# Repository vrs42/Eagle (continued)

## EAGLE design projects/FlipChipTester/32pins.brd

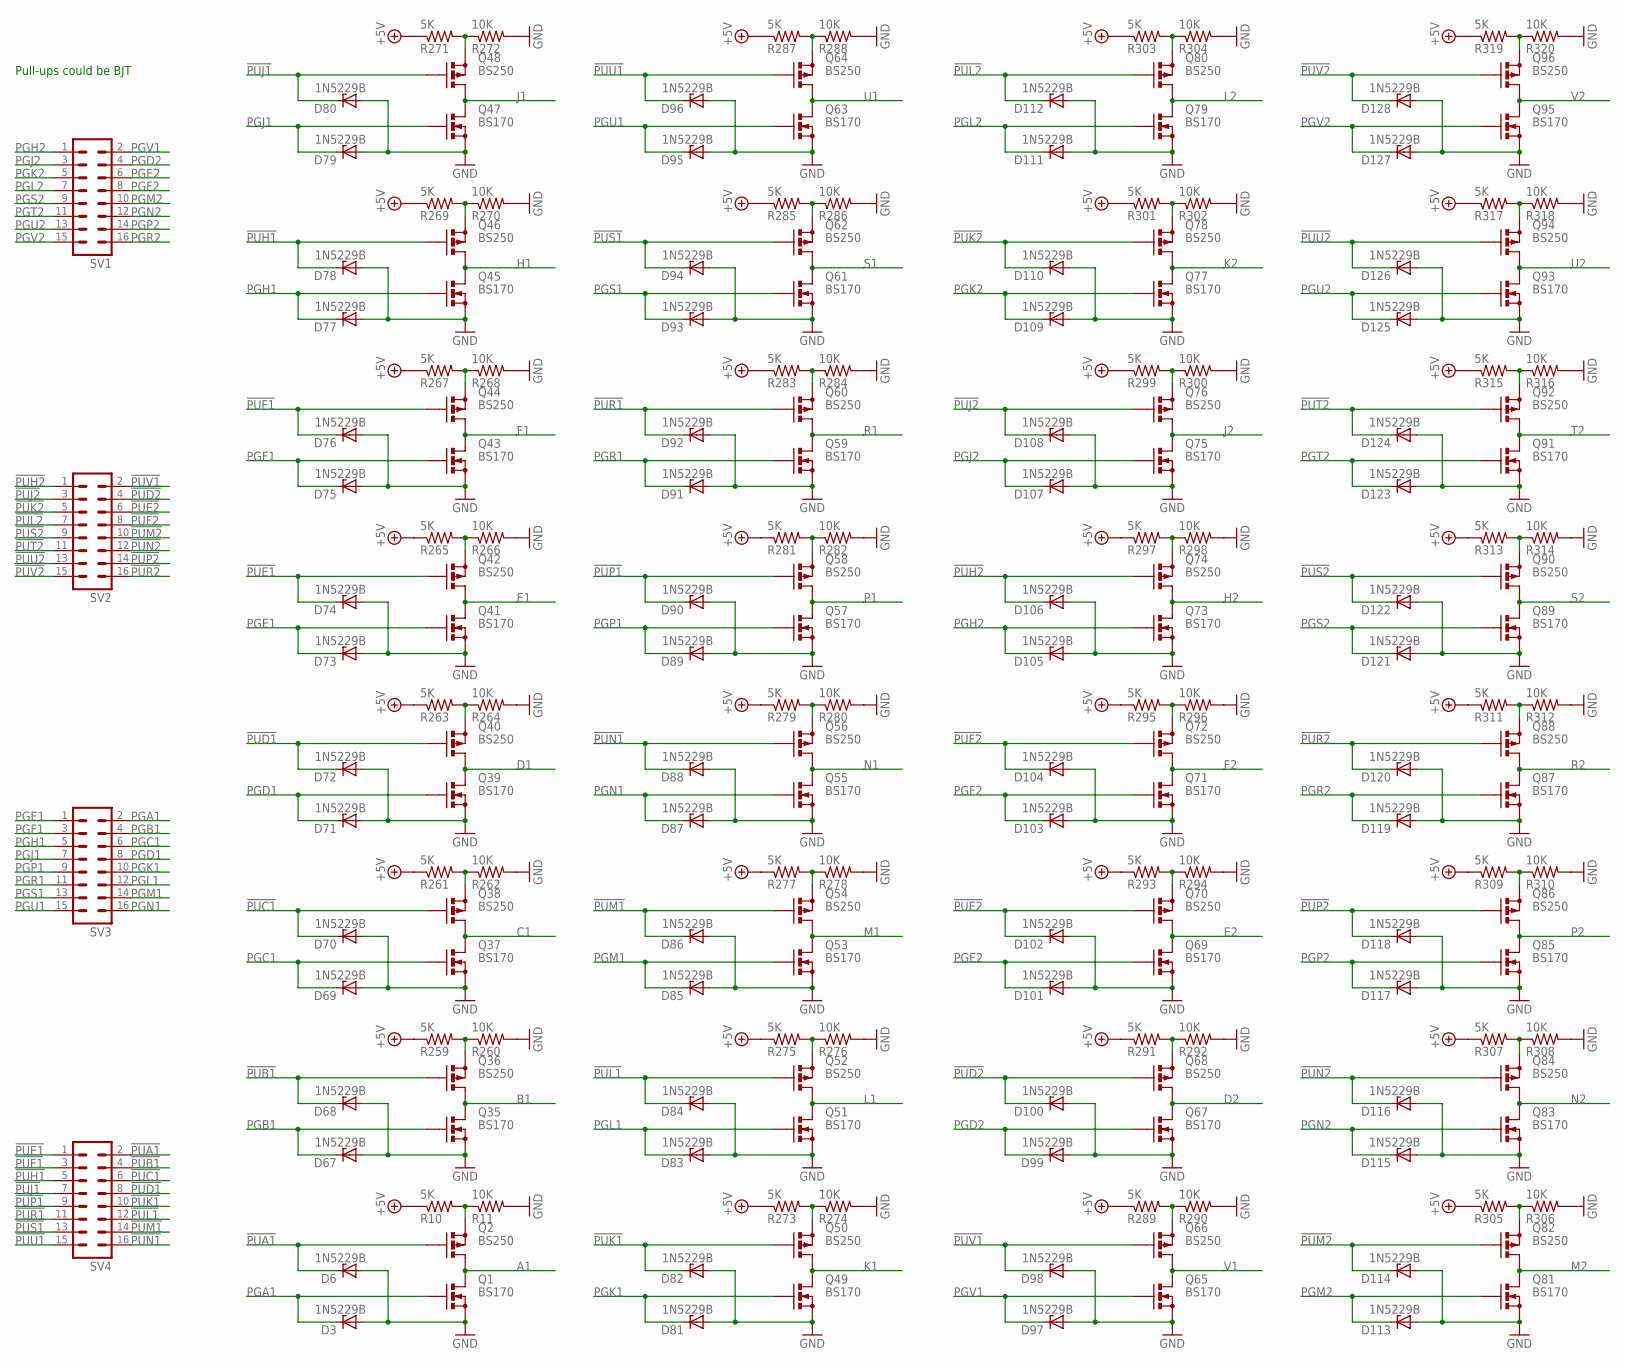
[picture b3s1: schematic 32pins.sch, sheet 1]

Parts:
D3, D6, D67, D68, D69, D70, D71, D72, D73, D74, D75, D76, D77, D78, D79, D80, D81, D82, D83, D84, D85, D86, D87, D88, D89, D90, D91, D92, D93, D94, D95, D96, D97, D98, D99, D100, D101, D102, D103, D104, D105, D106, D107, D108, D109, D110, D111, D112, D113, D114, D115, D116, D117, D118, D119, D120, D121, D122, D123, D124, D125, D126, D127, D128: 1N5229B; ZDIO-2.5
Q1, Q35, Q37, Q39, Q41, Q43, Q45, Q47, Q49, Q51, Q53, Q55, Q57, Q59, Q61, Q63, Q65, Q67, Q69, Q71, Q73, Q75, Q77, Q79, Q81, Q83, Q85, Q87, Q89, Q91, Q93, Q95: BS170; SOT54E
Q2, Q36, Q38, Q40, Q42, Q44, Q46, Q48, Q50, Q52, Q54, Q56, Q58, Q60, Q62, Q64, Q66, Q68, Q70, Q72, Q74, Q76, Q78, Q80, Q82, Q84, Q86, Q88, Q90, Q92, Q94, Q96: BS250; SOT54E
R10, R259, R261, R263, R265, R267, R269, R271, R273, R275, R277, R279, R281, R283, R285, R287, R289, R291, R293, R295, R297, R299, R301, R303, R305, R307, R309, R311, R313, R315, R317, R319: 5K; 0207/2V
R11, R260, R262, R264, R266, R268, R270, R272, R274, R276, R278, R280, R282, R284, R286, R288, R290, R292, R294, R296, R298, R300, R302, R304, R306, R308, R310, R312, R314, R316, R318, R320: 10K; 0207/2V
SV1, SV2, SV3, SV4: MA08-2

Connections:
!PUA1: D6.C, Q2.G, SV4.2
!PUB1: D68.C, Q36.G, SV4.4
!PUC1: D70.C, Q38.G, SV4.6
!PUD1: D72.C, Q40.G, SV4.8
!PUD2: D100.C, Q68.G, SV2.4
!PUE1: D74.C, Q42.G, SV4.1
!PUE2: D102.C, Q70.G, SV2.6
!PUF1: D76.C, Q44.G, SV4.3
!PUF2: D104.C, Q72.G, SV2.8
!PUH1: D78.C, Q46.G, SV4.5
!PUH2: D106.C, Q74.G, SV2.1
!PUJ1: D80.C, Q48.G, SV4.7
!PUJ2: D108.C, Q76.G, SV2.3
!PUK1: D82.C, Q50.G, SV4.10
!PUK2: D110.C, Q78.G, SV2.5
!PUL1: D84.C, Q52.G, SV4.12
!PUL2: D112.C, Q80.G, SV2.7
!PUM1: D86.C, Q54.G, SV4.14
!PUM2: D114.C, Q82.G, SV2.10
!PUN1: D88.C, Q56.G, SV4.16
!PUN2: D116.C, Q84.G, SV2.12
!PUP1: D90.C, Q58.G, SV4.9
!PUP2: D118.C, Q86.G, SV2.14
!PUR1: D92.C, Q60.G, SV4.11
!PUR2: D120.C, Q88.G, SV2.16
!PUS1: D94.C, Q62.G, SV4.13
!PUS2: D122.C, Q90.G, SV2.9
!PUT2: D124.C, Q92.G, SV2.11
!PUU1: D96.C, Q64.G, SV4.15
!PUU2: D126.C, Q94.G, SV2.13
!PUV1: D98.C, Q66.G, SV2.2
!PUV2: D128.C, Q96.G, SV2.15
+5V: R10.1, R259.1, R261.1, R263.1, R265.1, R267.1, R269.1, R271.1, R273.1, R275.1, R277.1, R279.1, R281.1, R283.1, R285.1, R287.1, R289.1, R291.1, R293.1, R295.1, R297.1, R299.1, R301.1, R303.1, R305.1, R307.1, R309.1, R311.1, R313.1, R315.1, R317.1, R319.1; also elsewhere on the board
A1: Q1.D, Q2.D; also elsewhere on the board
B1: Q35.D, Q36.D; also elsewhere on the board
C1: Q37.D, Q38.D; also elsewhere on the board
D1: Q39.D, Q40.D; also elsewhere on the board
D2: Q67.D, Q68.D; also elsewhere on the board
E1: Q41.D, Q42.D; also elsewhere on the board
E2: Q69.D, Q70.D; also elsewhere on the board
F1: Q43.D, Q44.D; also elsewhere on the board
F2: Q71.D, Q72.D; also elsewhere on the board
GND: D3.A, D6.A, D67.A, D68.A, D69.A, D70.A, D71.A, D72.A, D73.A, D74.A, D75.A, D76.A, D77.A, D78.A, D79.A, D80.A, D81.A, D82.A, D83.A, D84.A, D85.A, D86.A, D87.A, D88.A, D89.A, D90.A, D91.A, D92.A, D93.A, D94.A, D95.A, D96.A, D97.A, D98.A, D99.A, D100.A, D101.A, D102.A, D103.A, D104.A, D105.A, D106.A, D107.A, D108.A, D109.A, D110.A, D111.A, D112.A, D113.A, D114.A, D115.A, D116.A, D117.A, D118.A, D119.A, D120.A, D121.A, D122.A, D123.A, D124.A, D125.A, D126.A, D127.A, D128.A, Q1.S, Q35.S, Q37.S, Q39.S, Q41.S, Q43.S, Q45.S, Q47.S, Q49.S, Q51.S, Q53.S, Q55.S, Q57.S, Q59.S, Q61.S, Q63.S, Q65.S, Q67.S, Q69.S, Q71.S, Q73.S, Q75.S, Q77.S, Q79.S, Q81.S, Q83.S, Q85.S, Q87.S, Q89.S, Q91.S, Q93.S, Q95.S, R11.2, R260.2, R262.2, R264.2, R266.2, R268.2, R270.2, R272.2, R274.2, R276.2, R278.2, R280.2, R282.2, R284.2, R286.2, R288.2, R290.2, R292.2, R294.2, R296.2, R298.2, R300.2, R302.2, R304.2, R306.2, R308.2, R310.2, R312.2, R314.2, R316.2, R318.2, R320.2; also elsewhere on the board
H1: Q45.D, Q46.D; also elsewhere on the board
H2: Q73.D, Q74.D; also elsewhere on the board
J1: Q47.D, Q48.D; also elsewhere on the board
J2: Q75.D, Q76.D; also elsewhere on the board
K1: Q49.D, Q50.D; also elsewhere on the board
K2: Q77.D, Q78.D; also elsewhere on the board
L1: Q51.D, Q52.D; also elsewhere on the board
L2: Q79.D, Q80.D; also elsewhere on the board
M1: Q53.D, Q54.D; also elsewhere on the board
M2: Q81.D, Q82.D; also elsewhere on the board
N1: Q55.D, Q56.D; also elsewhere on the board
N2: Q83.D, Q84.D; also elsewhere on the board
unnamed: Q2.S, R10.2, R11.1
unnamed: Q36.S, R259.2, R260.1
unnamed: Q38.S, R261.2, R262.1
unnamed: Q40.S, R263.2, R264.1
unnamed: Q42.S, R265.2, R266.1
unnamed: Q44.S, R267.2, R268.1
unnamed: Q46.S, R269.2, R270.1
unnamed: Q48.S, R271.2, R272.1
unnamed: Q50.S, R273.2, R274.1
unnamed: Q52.S, R275.2, R276.1
unnamed: Q54.S, R277.2, R278.1
unnamed: Q56.S, R279.2, R280.1
unnamed: Q58.S, R281.2, R282.1
unnamed: Q60.S, R283.2, R284.1
unnamed: Q62.S, R285.2, R286.1
unnamed: Q64.S, R287.2, R288.1
unnamed: Q66.S, R289.2, R290.1
unnamed: Q68.S, R291.2, R292.1
unnamed: Q70.S, R293.2, R294.1
unnamed: Q72.S, R295.2, R296.1
unnamed: Q74.S, R297.2, R298.1
unnamed: Q76.S, R299.2, R300.1
unnamed: Q78.S, R301.2, R302.1
unnamed: Q80.S, R303.2, R304.1
unnamed: Q82.S, R305.2, R306.1
unnamed: Q84.S, R307.2, R308.1
unnamed: Q86.S, R309.2, R310.1
unnamed: Q88.S, R311.2, R312.1
unnamed: Q90.S, R313.2, R314.1
unnamed: Q92.S, R315.2, R316.1
unnamed: Q94.S, R317.2, R318.1
unnamed: Q96.S, R319.2, R320.1
P1: Q57.D, Q58.D; also elsewhere on the board
P2: Q85.D, Q86.D; also elsewhere on the board
PGA1: D3.C, Q1.G, SV3.2
PGB1: D67.C, Q35.G, SV3.4
PGC1: D69.C, Q37.G, SV3.6
PGD1: D71.C, Q39.G, SV3.8
PGD2: D99.C, Q67.G, SV1.4
PGE1: D73.C, Q41.G, SV3.1
PGE2: D101.C, Q69.G, SV1.6
PGF1: D75.C, Q43.G, SV3.3
PGF2: D103.C, Q71.G, SV1.8
PGH1: D77.C, Q45.G, SV3.5
PGH2: D105.C, Q73.G, SV1.1
PGJ1: D79.C, Q47.G, SV3.7
PGJ2: D107.C, Q75.G, SV1.3
PGK1: D81.C, Q49.G, SV3.10
PGK2: D109.C, Q77.G, SV1.5
PGL1: D83.C, Q51.G, SV3.12
PGL2: D111.C, Q79.G, SV1.7
PGM1: D85.C, Q53.G, SV3.14
PGM2: D113.C, Q81.G, SV1.10
PGN1: D87.C, Q55.G, SV3.16
PGN2: D115.C, Q83.G, SV1.12
PGP1: D89.C, Q57.G, SV3.9
PGP2: D117.C, Q85.G, SV1.14
PGR1: D91.C, Q59.G, SV3.11
PGR2: D119.C, Q87.G, SV1.16
PGS1: D93.C, Q61.G, SV3.13
PGS2: D121.C, Q89.G, SV1.9
PGT2: D123.C, Q91.G, SV1.11
PGU1: D95.C, Q63.G, SV3.15
PGU2: D125.C, Q93.G, SV1.13
PGV1: D97.C, Q65.G, SV1.2
PGV2: D127.C, Q95.G, SV1.15
R1: Q59.D, Q60.D; also elsewhere on the board
R2: Q87.D, Q88.D; also elsewhere on the board
S1: Q61.D, Q62.D; also elsewhere on the board
S2: Q89.D, Q90.D; also elsewhere on the board
T2: Q91.D, Q92.D; also elsewhere on the board
U1: Q63.D, Q64.D; also elsewhere on the board
U2: Q93.D, Q94.D; also elsewhere on the board
V1: Q65.D, Q66.D; also elsewhere on the board
V2: Q95.D, Q96.D; also elsewhere on the board

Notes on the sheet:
Pull-ups could be BJT

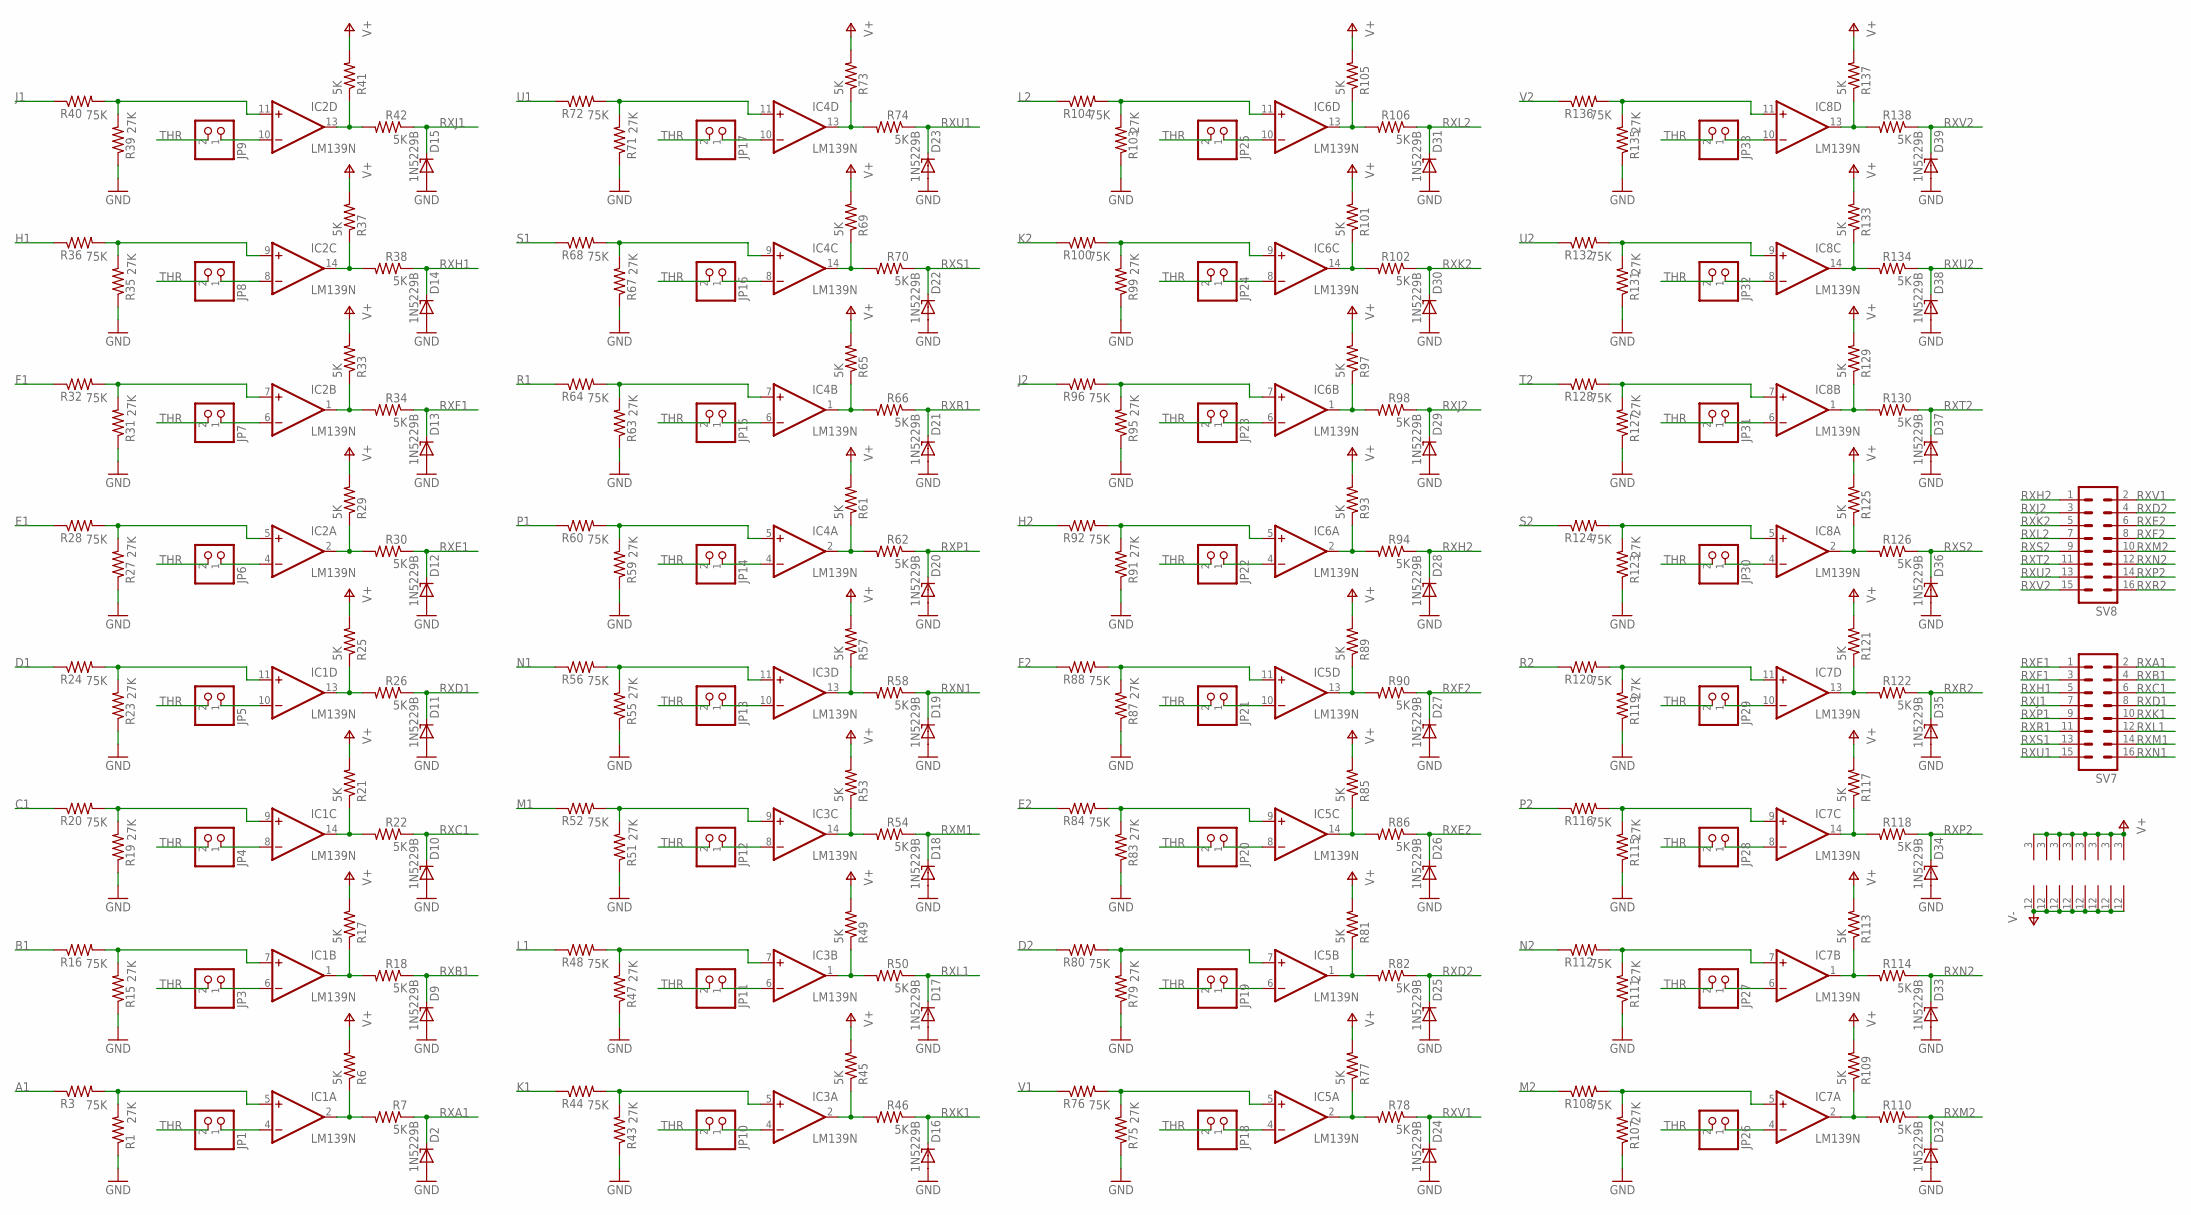
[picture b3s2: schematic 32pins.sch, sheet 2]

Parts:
D2, D9, D10, D11, D12, D13, D14, D15, D16, D17, D18, D19, D20, D21, D22, D23, D24, D25, D26, D27, D28, D29, D30, D31, D32, D33, D34, D35, D36, D37, D38, D39: 1N5229B; ZDIO-2.5
IC1, IC2, IC3, IC4, IC5, IC6, IC7, IC8: LM139N; DIL14
JP1, JP3, JP4, JP5, JP6, JP7, JP8, JP9, JP10, JP11, JP12, JP13, JP14, JP15, JP16, JP17, JP18, JP19, JP20, JP21, JP22, JP23, JP24, JP25, JP26, JP27, JP28, JP29, JP30, JP31, JP32, JP33: PINHD-1X2; 1X02
R1, R15, R19, R23, R27, R31, R35, R39, R43, R47, R51, R55, R59, R63, R67, R71, R75, R79, R83, R87, R91, R95, R99, R103, R107, R111, R115, R119, R123, R127, R131, R135: 27K; 0207/2V
R3, R16, R20, R24, R28, R32, R36, R40, R44, R48, R52, R56, R60, R64, R68, R72, R76, R80, R84, R88, R92, R96, R100, R104, R108, R112, R116, R120, R124, R128, R132, R136: 75K; 0207/2V
R6, R7, R17, R18, R21, R22, R25, R26, R29, R30, R33, R34, R37, R38, R41, R42, R45, R46, R49, R50, R53, R54, R57, R58, R61, R62, R65, R66, R69, R70, R73, R74, R77, R78, R81, R82, R85, R86, R89, R90, R93, R94, R97, R98, R101, R102, R105, R106, R109, R110, R113, R114, R117, R118, R121, R122, R125, R126, R129, R130, R133, R134, R137, R138: 5K; 0207/2V
SV7, SV8: MA08-2

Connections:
A1: R3.1; also elsewhere on the board
B1: R16.1; also elsewhere on the board
C1: R20.1; also elsewhere on the board
D1: R24.1; also elsewhere on the board
D2: R80.1; also elsewhere on the board
E1: R28.1; also elsewhere on the board
E2: R84.1; also elsewhere on the board
F1: R32.1; also elsewhere on the board
F2: R88.1; also elsewhere on the board
GND: D2.A, D9.A, D10.A, D11.A, D12.A, D13.A, D14.A, D15.A, D16.A, D17.A, D18.A, D19.A, D20.A, D21.A, D22.A, D23.A, D24.A, D25.A, D26.A, D27.A, D28.A, D29.A, D30.A, D31.A, D32.A, D33.A, D34.A, D35.A, D36.A, D37.A, D38.A, D39.A, R1.1, R15.1, R19.1, R23.1, R27.1, R31.1, R35.1, R39.1, R43.1, R47.1, R51.1, R55.1, R59.1, R63.1, R67.1, R71.1, R75.1, R79.1, R83.1, R87.1, R91.1, R95.1, R99.1, R103.1, R107.1, R111.1, R115.1, R119.1, R123.1, R127.1, R131.1, R135.1; also elsewhere on the board
H1: R36.1; also elsewhere on the board
H2: R92.1; also elsewhere on the board
J1: R40.1; also elsewhere on the board
J2: R96.1; also elsewhere on the board
K1: R44.1; also elsewhere on the board
K2: R100.1; also elsewhere on the board
L1: R48.1; also elsewhere on the board
L2: R104.1; also elsewhere on the board
M1: R52.1; also elsewhere on the board
M2: R108.1; also elsewhere on the board
N1: R56.1; also elsewhere on the board
N2: R112.1; also elsewhere on the board
unnamed: IC1.5 (+IN), R1.2, R3.2
unnamed: IC1.4 (-IN), JP1.1
unnamed: IC1.2 (OUT), R6.1, R7.2
unnamed: IC1.7 (+IN), R15.2, R16.2
unnamed: IC1.6 (-IN), JP3.1
unnamed: IC1.1 (OUT), R17.1, R18.2
unnamed: IC1.9 (+IN), R19.2, R20.2
unnamed: IC1.8 (-IN), JP4.1
unnamed: IC1.14 (OUT), R21.1, R22.2
unnamed: IC1.11 (+IN), R23.2, R24.2
unnamed: IC1.10 (-IN), JP5.1
unnamed: IC1.13 (OUT), R25.1, R26.2
unnamed: IC2.5 (+IN), R27.2, R28.2
unnamed: IC2.4 (-IN), JP6.1
unnamed: IC2.2 (OUT), R29.1, R30.2
unnamed: IC2.7 (+IN), R31.2, R32.2
unnamed: IC2.6 (-IN), JP7.1
unnamed: IC2.1 (OUT), R33.1, R34.2
unnamed: IC2.9 (+IN), R35.2, R36.2
unnamed: IC2.8 (-IN), JP8.1
unnamed: IC2.14 (OUT), R37.1, R38.2
unnamed: IC2.11 (+IN), R39.2, R40.2
unnamed: IC2.10 (-IN), JP9.1
unnamed: IC2.13 (OUT), R41.1, R42.2
unnamed: IC3.5 (+IN), R43.2, R44.2
unnamed: IC3.4 (-IN), JP10.1
unnamed: IC3.2 (OUT), R45.1, R46.2
unnamed: IC3.7 (+IN), R47.2, R48.2
unnamed: IC3.6 (-IN), JP11.1
unnamed: IC3.1 (OUT), R49.1, R50.2
unnamed: IC3.9 (+IN), R51.2, R52.2
unnamed: IC3.8 (-IN), JP12.1
unnamed: IC3.14 (OUT), R53.1, R54.2
unnamed: IC3.11 (+IN), R55.2, R56.2
unnamed: IC3.10 (-IN), JP13.1
unnamed: IC3.13 (OUT), R57.1, R58.2
unnamed: IC4.5 (+IN), R59.2, R60.2
unnamed: IC4.4 (-IN), JP14.1
unnamed: IC4.2 (OUT), R61.1, R62.2
unnamed: IC4.7 (+IN), R63.2, R64.2
unnamed: IC4.6 (-IN), JP15.1
unnamed: IC4.1 (OUT), R65.1, R66.2
unnamed: IC4.9 (+IN), R67.2, R68.2
unnamed: IC4.8 (-IN), JP16.1
unnamed: IC4.14 (OUT), R69.1, R70.2
unnamed: IC4.11 (+IN), R71.2, R72.2
unnamed: IC4.10 (-IN), JP17.1
unnamed: IC4.13 (OUT), R73.1, R74.2
unnamed: IC5.5 (+IN), R75.2, R76.2
unnamed: IC5.4 (-IN), JP18.1
unnamed: IC5.2 (OUT), R77.1, R78.2
unnamed: IC5.7 (+IN), R79.2, R80.2
unnamed: IC5.6 (-IN), JP19.1
unnamed: IC5.1 (OUT), R81.1, R82.2
unnamed: IC5.9 (+IN), R83.2, R84.2
unnamed: IC5.8 (-IN), JP20.1
unnamed: IC5.14 (OUT), R85.1, R86.2
unnamed: IC5.11 (+IN), R87.2, R88.2
unnamed: IC5.10 (-IN), JP21.1
unnamed: IC5.13 (OUT), R89.1, R90.2
unnamed: IC6.5 (+IN), R91.2, R92.2
unnamed: IC6.4 (-IN), JP22.1
unnamed: IC6.2 (OUT), R93.1, R94.2
unnamed: IC6.7 (+IN), R95.2, R96.2
unnamed: IC6.6 (-IN), JP23.1
unnamed: IC6.1 (OUT), R97.1, R98.2
unnamed: IC6.9 (+IN), R99.2, R100.2
unnamed: IC6.8 (-IN), JP24.1
unnamed: IC6.14 (OUT), R101.1, R102.2
unnamed: IC6.11 (+IN), R103.2, R104.2
unnamed: IC6.10 (-IN), JP25.1
unnamed: IC6.13 (OUT), R105.1, R106.2
unnamed: IC7.5 (+IN), R107.2, R108.2
unnamed: IC7.4 (-IN), JP26.1
unnamed: IC7.2 (OUT), R109.1, R110.2
unnamed: IC7.7 (+IN), R111.2, R112.2
unnamed: IC7.6 (-IN), JP27.1
unnamed: IC7.1 (OUT), R113.1, R114.2
unnamed: IC7.9 (+IN), R115.2, R116.2
unnamed: IC7.8 (-IN), JP28.1
unnamed: IC7.14 (OUT), R117.1, R118.2
unnamed: IC7.11 (+IN), R119.2, R120.2
unnamed: IC7.10 (-IN), JP29.1
unnamed: IC7.13 (OUT), R121.1, R122.2
unnamed: IC8.5 (+IN), R123.2, R124.2
unnamed: IC8.4 (-IN), JP30.1
unnamed: IC8.2 (OUT), R125.1, R126.2
unnamed: IC8.7 (+IN), R127.2, R128.2
unnamed: IC8.6 (-IN), JP31.1
unnamed: IC8.1 (OUT), R129.1, R130.2
unnamed: IC8.9 (+IN), R131.2, R132.2
unnamed: IC8.8 (-IN), JP32.1
unnamed: IC8.14 (OUT), R133.1, R134.2
unnamed: IC8.11 (+IN), R135.2, R136.2
unnamed: IC8.10 (-IN), JP33.1
unnamed: IC8.13 (OUT), R137.1, R138.2
P1: R60.1; also elsewhere on the board
P2: R116.1; also elsewhere on the board
R1: R64.1; also elsewhere on the board
R2: R120.1; also elsewhere on the board
RXA1: D2.C, R7.1, SV7.2
RXB1: D9.C, R18.1, SV7.4
RXC1: D10.C, R22.1, SV7.6
RXD1: D11.C, R26.1, SV7.8
RXD2: D25.C, R82.1, SV8.4
RXE1: D12.C, R30.1, SV7.1
RXE2: D26.C, R86.1, SV8.6
RXF1: D13.C, R34.1, SV7.3
RXF2: D27.C, R90.1, SV8.8
RXH1: D14.C, R38.1, SV7.5
RXH2: D28.C, R94.1, SV8.1
RXJ1: D15.C, R42.1, SV7.7
RXJ2: D29.C, R98.1, SV8.3
RXK1: D16.C, R46.1, SV7.10
RXK2: D30.C, R102.1, SV8.5
RXL1: D17.C, R50.1, SV7.12
RXL2: D31.C, R106.1, SV8.7
RXM1: D18.C, R54.1, SV7.14
RXM2: D32.C, R110.1, SV8.10
RXN1: D19.C, R58.1, SV7.16
RXN2: D33.C, R114.1, SV8.12
RXP1: D20.C, R62.1, SV7.9
RXP2: D34.C, R118.1, SV8.14
RXR1: D21.C, R66.1, SV7.11
RXR2: D35.C, R122.1, SV8.16
RXS1: D22.C, R70.1, SV7.13
RXS2: D36.C, R126.1, SV8.9
RXT2: D37.C, R130.1, SV8.11
RXU1: D23.C, R74.1, SV7.15
RXU2: D38.C, R134.1, SV8.13
RXV1: D24.C, R78.1, SV8.2
RXV2: D39.C, R138.1, SV8.15
S1: R68.1; also elsewhere on the board
S2: R124.1; also elsewhere on the board
T2: R128.1; also elsewhere on the board
THR: JP1.2, JP3.2, JP4.2, JP5.2, JP6.2, JP7.2, JP8.2, JP9.2, JP10.2, JP11.2, JP12.2, JP13.2, JP14.2, JP15.2, JP16.2, JP17.2, JP18.2, JP19.2, JP20.2, JP21.2, JP22.2, JP23.2, JP24.2, JP25.2, JP26.2, JP27.2, JP28.2, JP29.2, JP30.2, JP31.2, JP32.2, JP33.2; also elsewhere on the board
U1: R72.1; also elsewhere on the board
U2: R132.1; also elsewhere on the board
V1: R76.1; also elsewhere on the board
V2: R136.1; also elsewhere on the board
V+: IC1.3 (V+), IC2.3 (V+), IC3.3 (V+), IC4.3 (V+), IC5.3 (V+), IC6.3 (V+), IC7.3 (V+), IC8.3 (V+), R6.2, R17.2, R21.2, R25.2, R29.2, R33.2, R37.2, R41.2, R45.2, R49.2, R53.2, R57.2, R61.2, R65.2, R69.2, R73.2, R77.2, R81.2, R85.2, R89.2, R93.2, R97.2, R101.2, R105.2, R109.2, R113.2, R117.2, R121.2, R125.2, R129.2, R133.2, R137.2; also elsewhere on the board
V-: IC1.12 (GND), IC2.12 (GND), IC3.12 (GND), IC4.12 (GND), IC5.12 (GND), IC6.12 (GND), IC7.12 (GND), IC8.12 (GND); also elsewhere on the board

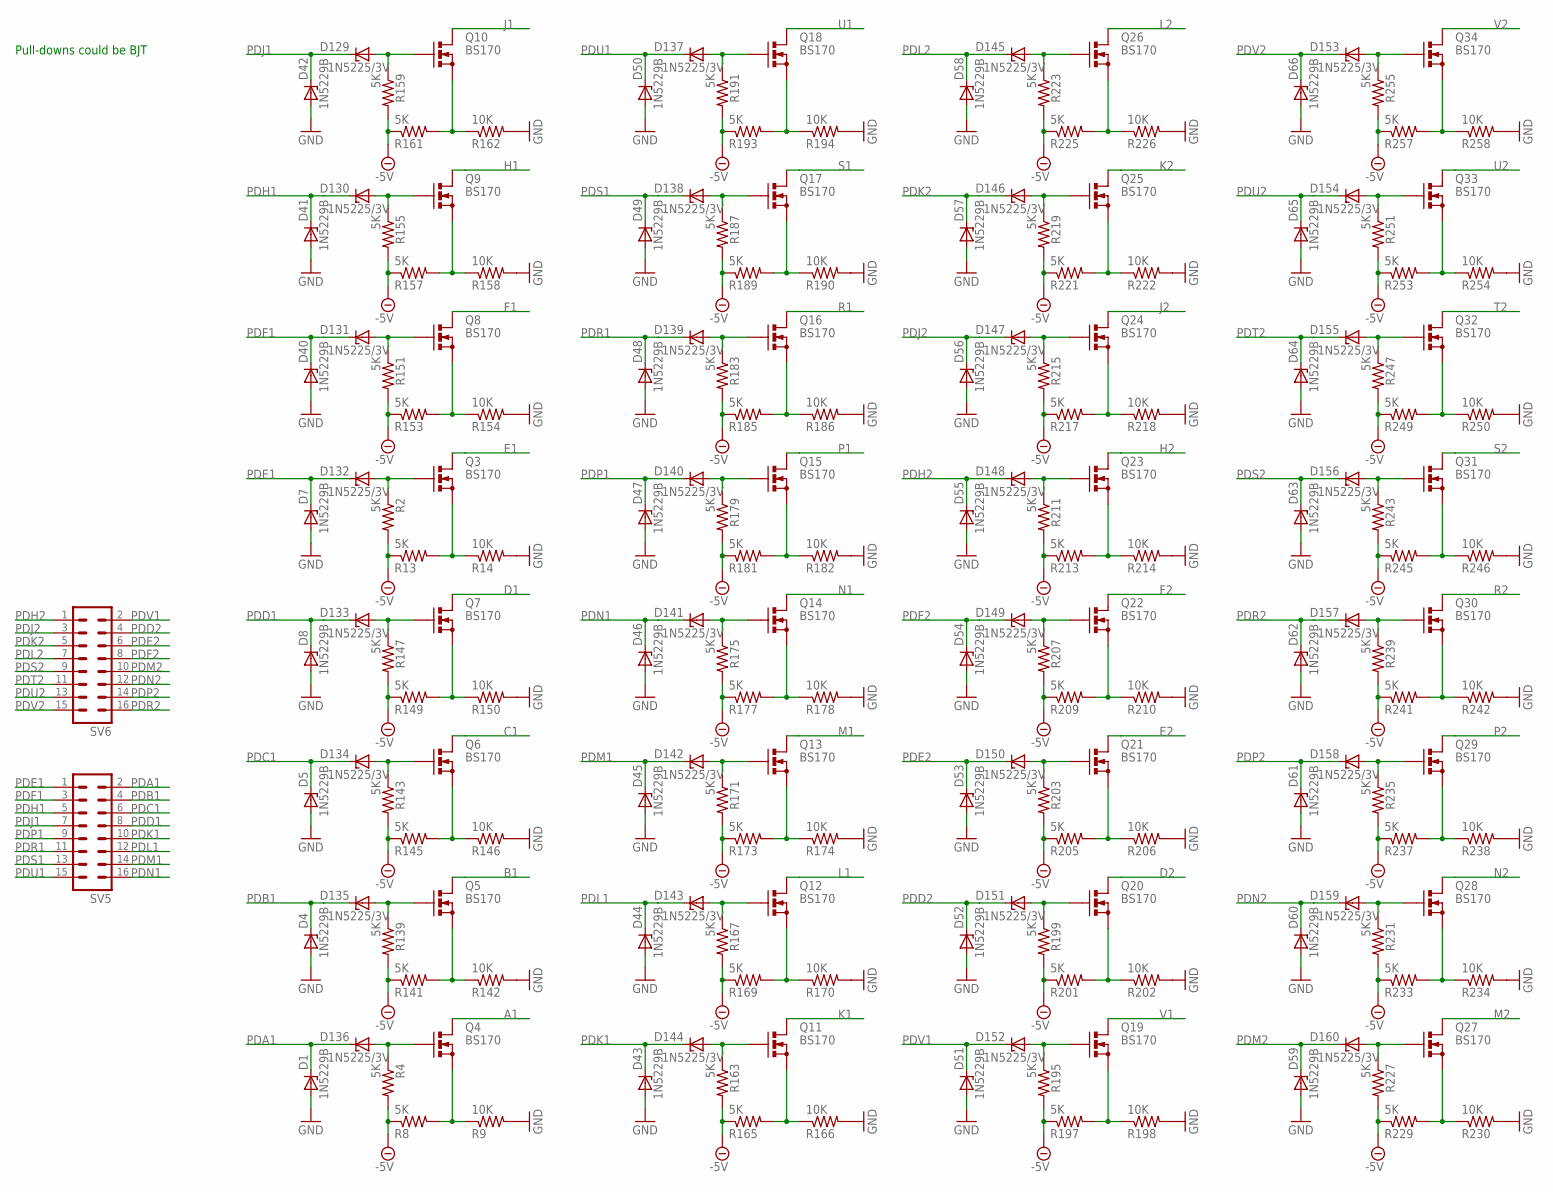
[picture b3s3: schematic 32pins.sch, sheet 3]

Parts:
D1, D4, D5, D7, D8, D40, D41, D42, D43, D44, D45, D46, D47, D48, D49, D50, D51, D52, D53, D54, D55, D56, D57, D58, D59, D60, D61, D62, D63, D64, D65, D66: 1N5229B; ZDIO-2.5
D129, D130, D131, D132, D133, D134, D135, D136, D137, D138, D139, D140, D141, D142, D143, D144, D145, D146, D147, D148, D149, D150, D151, D152, D153, D154, D155, D156, D157, D158, D159, D160: 1N5225/3V; ZDIO-2.5
Q3, Q4, Q5, Q6, Q7, Q8, Q9, Q10, Q11, Q12, Q13, Q14, Q15, Q16, Q17, Q18, Q19, Q20, Q21, Q22, Q23, Q24, Q25, Q26, Q27, Q28, Q29, Q30, Q31, Q32, Q33, Q34: BS170; SOT54E
R2, R4, R8, R13, R139, R141, R143, R145, R147, R149, R151, R153, R155, R157, R159, R161, R163, R165, R167, R169, R171, R173, R175, R177, R179, R181, R183, R185, R187, R189, R191, R193, R195, R197, R199, R201, R203, R205, R207, R209, R211, R213, R215, R217, R219, R221, R223, R225, R227, R229, R231, R233, R235, R237, R239, R241, R243, R245, R247, R249, R251, R253, R255, R257: 5K; 0207/2V
R9, R14, R142, R146, R150, R154, R158, R162, R166, R170, R174, R178, R182, R186, R190, R194, R198, R202, R206, R210, R214, R218, R222, R226, R230, R234, R238, R242, R246, R250, R254, R258: 10K; 0207/2V
SV5, SV6: MA08-2

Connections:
-5V: R2.2, R4.2, R8.1, R13.1, R139.2, R141.1, R143.2, R145.1, R147.2, R149.1, R151.2, R153.1, R155.2, R157.1, R159.2, R161.1, R163.2, R165.1, R167.2, R169.1, R171.2, R173.1, R175.2, R177.1, R179.2, R181.1, R183.2, R185.1, R187.2, R189.1, R191.2, R193.1, R195.2, R197.1, R199.2, R201.1, R203.2, R205.1, R207.2, R209.1, R211.2, R213.1, R215.2, R217.1, R219.2, R221.1, R223.2, R225.1, R227.2, R229.1, R231.2, R233.1, R235.2, R237.1, R239.2, R241.1, R243.2, R245.1, R247.2, R249.1, R251.2, R253.1, R255.2, R257.1; also elsewhere on the board
A1: Q4.D; also elsewhere on the board
B1: Q5.D; also elsewhere on the board
C1: Q6.D; also elsewhere on the board
D1: Q7.D; also elsewhere on the board
D2: Q20.D; also elsewhere on the board
E1: Q3.D; also elsewhere on the board
E2: Q21.D; also elsewhere on the board
F1: Q8.D; also elsewhere on the board
F2: Q22.D; also elsewhere on the board
GND: D1.A, D4.A, D5.A, D7.A, D8.A, D40.A, D41.A, D42.A, D43.A, D44.A, D45.A, D46.A, D47.A, D48.A, D49.A, D50.A, D51.A, D52.A, D53.A, D54.A, D55.A, D56.A, D57.A, D58.A, D59.A, D60.A, D61.A, D62.A, D63.A, D64.A, D65.A, D66.A, R9.2, R14.2, R142.2, R146.2, R150.2, R154.2, R158.2, R162.2, R166.2, R170.2, R174.2, R178.2, R182.2, R186.2, R190.2, R194.2, R198.2, R202.2, R206.2, R210.2, R214.2, R218.2, R222.2, R226.2, R230.2, R234.2, R238.2, R242.2, R246.2, R250.2, R254.2, R258.2; also elsewhere on the board
H1: Q9.D; also elsewhere on the board
H2: Q23.D; also elsewhere on the board
J1: Q10.D; also elsewhere on the board
J2: Q24.D; also elsewhere on the board
K1: Q11.D; also elsewhere on the board
K2: Q25.D; also elsewhere on the board
L1: Q12.D; also elsewhere on the board
L2: Q26.D; also elsewhere on the board
M1: Q13.D; also elsewhere on the board
M2: Q27.D; also elsewhere on the board
N1: Q14.D; also elsewhere on the board
N2: Q28.D; also elsewhere on the board
unnamed: D132.A, Q3.G, R2.1
unnamed: D136.A, Q4.G, R4.1
unnamed: Q4.S, R8.2, R9.1
unnamed: D135.A, Q5.G, R139.1
unnamed: Q5.S, R141.2, R142.1
unnamed: Q3.S, R13.2, R14.1
unnamed: D134.A, Q6.G, R143.1
unnamed: Q6.S, R145.2, R146.1
unnamed: D133.A, Q7.G, R147.1
unnamed: Q7.S, R149.2, R150.1
unnamed: D131.A, Q8.G, R151.1
unnamed: Q8.S, R153.2, R154.1
unnamed: D130.A, Q9.G, R155.1
unnamed: Q9.S, R157.2, R158.1
unnamed: D129.A, Q10.G, R159.1
unnamed: Q10.S, R161.2, R162.1
unnamed: D144.A, Q11.G, R163.1
unnamed: Q11.S, R165.2, R166.1
unnamed: D143.A, Q12.G, R167.1
unnamed: Q12.S, R169.2, R170.1
unnamed: D142.A, Q13.G, R171.1
unnamed: Q13.S, R173.2, R174.1
unnamed: D141.A, Q14.G, R175.1
unnamed: Q14.S, R177.2, R178.1
unnamed: D140.A, Q15.G, R179.1
unnamed: Q15.S, R181.2, R182.1
unnamed: D139.A, Q16.G, R183.1
unnamed: Q16.S, R185.2, R186.1
unnamed: D138.A, Q17.G, R187.1
unnamed: Q17.S, R189.2, R190.1
unnamed: D137.A, Q18.G, R191.1
unnamed: Q18.S, R193.2, R194.1
unnamed: D152.A, Q19.G, R195.1
unnamed: Q19.S, R197.2, R198.1
unnamed: D151.A, Q20.G, R199.1
unnamed: Q20.S, R201.2, R202.1
unnamed: D150.A, Q21.G, R203.1
unnamed: Q21.S, R205.2, R206.1
unnamed: D149.A, Q22.G, R207.1
unnamed: Q22.S, R209.2, R210.1
unnamed: D148.A, Q23.G, R211.1
unnamed: Q23.S, R213.2, R214.1
unnamed: D147.A, Q24.G, R215.1
unnamed: Q24.S, R217.2, R218.1
unnamed: D146.A, Q25.G, R219.1
unnamed: Q25.S, R221.2, R222.1
unnamed: D145.A, Q26.G, R223.1
unnamed: Q26.S, R225.2, R226.1
unnamed: D160.A, Q27.G, R227.1
unnamed: Q27.S, R229.2, R230.1
unnamed: D159.A, Q28.G, R231.1
unnamed: Q28.S, R233.2, R234.1
unnamed: D158.A, Q29.G, R235.1
unnamed: Q29.S, R237.2, R238.1
unnamed: D157.A, Q30.G, R239.1
unnamed: Q30.S, R241.2, R242.1
unnamed: D156.A, Q31.G, R243.1
unnamed: Q31.S, R245.2, R246.1
unnamed: D155.A, Q32.G, R247.1
unnamed: Q32.S, R249.2, R250.1
unnamed: D154.A, Q33.G, R251.1
unnamed: Q33.S, R253.2, R254.1
unnamed: D153.A, Q34.G, R255.1
unnamed: Q34.S, R257.2, R258.1
P1: Q15.D; also elsewhere on the board
P2: Q29.D; also elsewhere on the board
PDA1: D1.C, D136.C, SV5.2
PDB1: D4.C, D135.C, SV5.4
PDC1: D5.C, D134.C, SV5.6
PDD1: D8.C, D133.C, SV5.8
PDD2: D52.C, D151.C, SV6.4
PDE1: D7.C, D132.C, SV5.1
PDE2: D53.C, D150.C, SV6.6
PDF1: D40.C, D131.C, SV5.3
PDF2: D54.C, D149.C, SV6.8
PDH1: D41.C, D130.C, SV5.5
PDH2: D55.C, D148.C, SV6.1
PDJ1: D42.C, D129.C, SV5.7
PDJ2: D56.C, D147.C, SV6.3
PDK1: D43.C, D144.C, SV5.10
PDK2: D57.C, D146.C, SV6.5
PDL1: D44.C, D143.C, SV5.12
PDL2: D58.C, D145.C, SV6.7
PDM1: D45.C, D142.C, SV5.14
PDM2: D59.C, D160.C, SV6.10
PDN1: D46.C, D141.C, SV5.16
PDN2: D60.C, D159.C, SV6.12
PDP1: D47.C, D140.C, SV5.9
PDP2: D61.C, D158.C, SV6.14
PDR1: D48.C, D139.C, SV5.11
PDR2: D62.C, D157.C, SV6.16
PDS1: D49.C, D138.C, SV5.13
PDS2: D63.C, D156.C, SV6.9
PDT2: D64.C, D155.C, SV6.11
PDU1: D50.C, D137.C, SV5.15
PDU2: D65.C, D154.C, SV6.13
PDV1: D51.C, D152.C, SV6.2
PDV2: D66.C, D153.C, SV6.15
R1: Q16.D; also elsewhere on the board
R2: Q30.D; also elsewhere on the board
S1: Q17.D; also elsewhere on the board
S2: Q31.D; also elsewhere on the board
T2: Q32.D; also elsewhere on the board
U1: Q18.D; also elsewhere on the board
U2: Q33.D; also elsewhere on the board
V1: Q19.D; also elsewhere on the board
V2: Q34.D; also elsewhere on the board

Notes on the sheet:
Pull-downs could be BJT

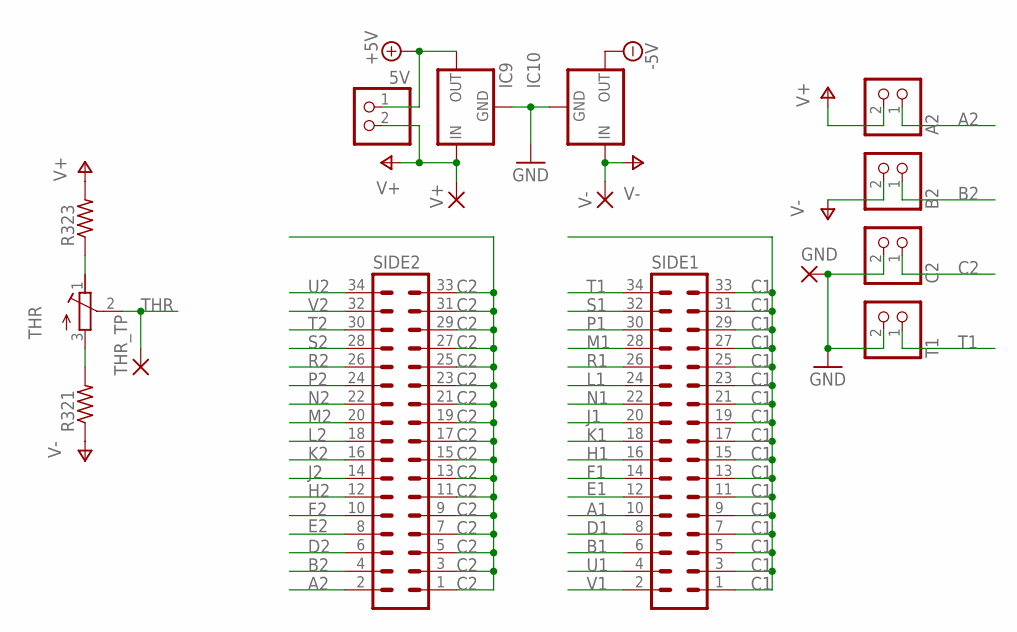
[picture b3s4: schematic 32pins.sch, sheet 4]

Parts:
5V: PINHD-1X2; 1X02
A2: PINHD-1X2; 1X02
B2: PINHD-1X2; 1X02
C2: PINHD-1X2; 1X02
GND: 1,6/0,9
IC9: 78XXL
IC10: 79XXL
R321, R323: R-US_0207/2V; 0207/2V
SIDE1, SIDE2: MA17-2
T1: PINHD-1X2; 1X02
THR: R-TRIMMT18; RTRIMT18
THR_TP: 1,6/0,9
V+: 1,6/0,9
V-: 1,6/0,9

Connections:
+5V: 5V.1, IC9.OUT; also elsewhere on the board
-5V: IC10.OUT; also elsewhere on the board
A1: SIDE1.10; also elsewhere on the board
A2: A2.1, SIDE2.2
B1: SIDE1.6; also elsewhere on the board
B2: B2.1, SIDE2.4
C1: SIDE1.1, SIDE1.3, SIDE1.5, SIDE1.7, SIDE1.9, SIDE1.11, SIDE1.13, SIDE1.15, SIDE1.17, SIDE1.19, SIDE1.21, SIDE1.23, SIDE1.25, SIDE1.27, SIDE1.29, SIDE1.31, SIDE1.33; also elsewhere on the board
C2: C2.1, SIDE2.1, SIDE2.3, SIDE2.5, SIDE2.7, SIDE2.9, SIDE2.11, SIDE2.13, SIDE2.15, SIDE2.17, SIDE2.19, SIDE2.21, SIDE2.23, SIDE2.25, SIDE2.27, SIDE2.29, SIDE2.31, SIDE2.33
D1: SIDE1.8; also elsewhere on the board
D2: SIDE2.6; also elsewhere on the board
E1: SIDE1.12; also elsewhere on the board
E2: SIDE2.8; also elsewhere on the board
F1: SIDE1.14; also elsewhere on the board
F2: SIDE2.10; also elsewhere on the board
GND: C2.2, GND.1, IC9.GND, IC10.GND, T1.2; also elsewhere on the board
H1: SIDE1.16; also elsewhere on the board
H2: SIDE2.12; also elsewhere on the board
J1: SIDE1.20; also elsewhere on the board
J2: SIDE2.14; also elsewhere on the board
K1: SIDE1.18; also elsewhere on the board
K2: SIDE2.16; also elsewhere on the board
L1: SIDE1.24; also elsewhere on the board
L2: SIDE2.18; also elsewhere on the board
M1: SIDE1.28; also elsewhere on the board
M2: SIDE2.20; also elsewhere on the board
N1: SIDE1.22; also elsewhere on the board
N2: SIDE2.22; also elsewhere on the board
unnamed: R321.2, THR.3 (A)
unnamed: R323.1, THR.1 (E)
P1: SIDE1.30; also elsewhere on the board
P2: SIDE2.24; also elsewhere on the board
R1: SIDE1.26; also elsewhere on the board
R2: SIDE2.26; also elsewhere on the board
S1: SIDE1.32; also elsewhere on the board
S2: SIDE2.28; also elsewhere on the board
T1: SIDE1.34, T1.1
T2: SIDE2.30; also elsewhere on the board
THR: THR.2 (S), THR_TP.1; also elsewhere on the board
U1: SIDE1.4; also elsewhere on the board
U2: SIDE2.34; also elsewhere on the board
V1: SIDE1.2; also elsewhere on the board
V2: SIDE2.32; also elsewhere on the board
V+: 5V.2, A2.2, IC9.IN, R323.2, V+.1; also elsewhere on the board
V-: B2.2, IC10.IN, R321.1, V-.1; also elsewhere on the board

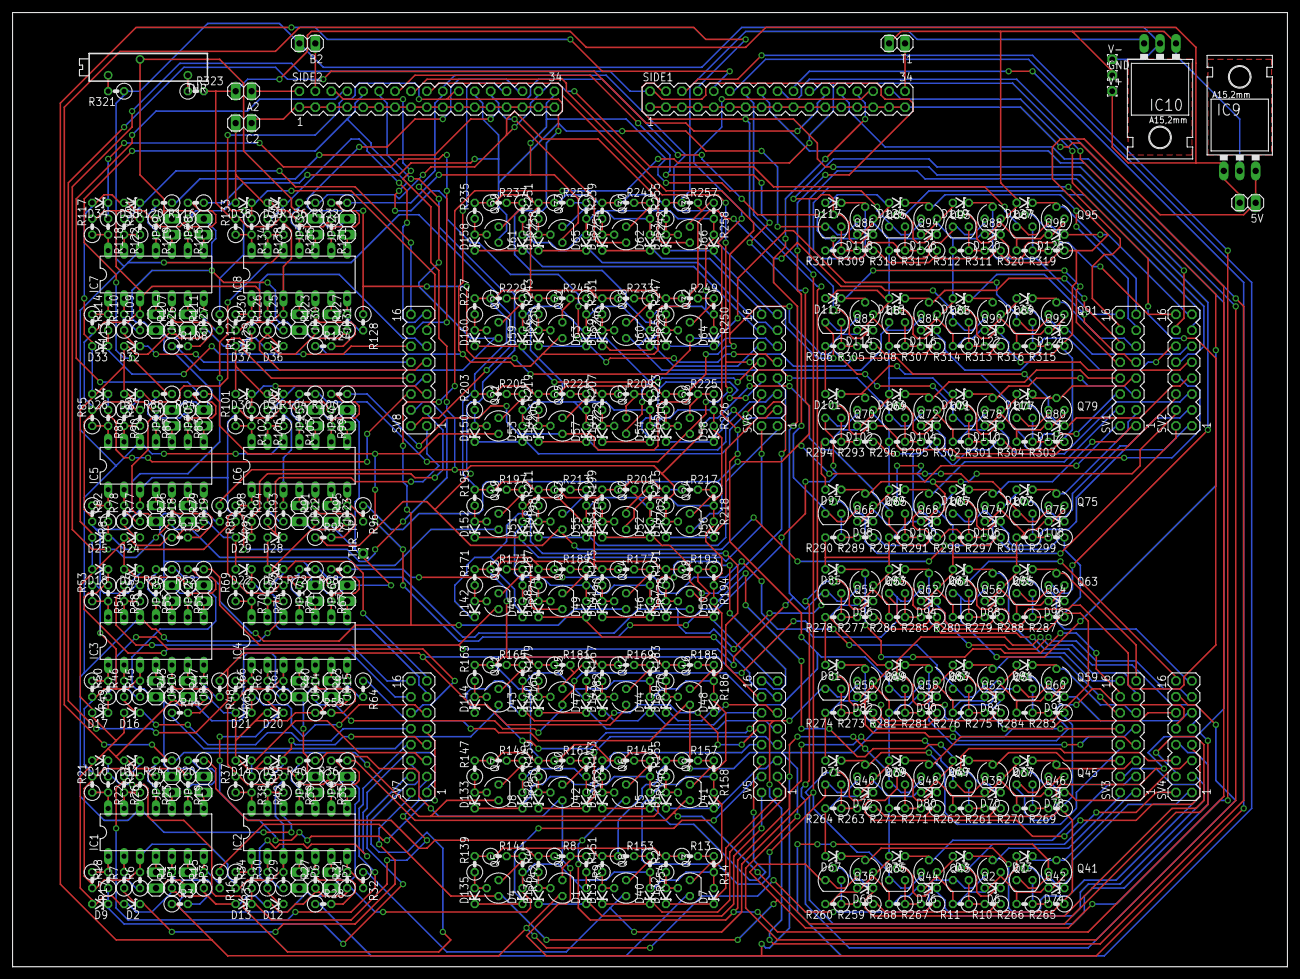
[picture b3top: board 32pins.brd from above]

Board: 2 copper layers, 203.2 x 152.1 mm, 608 parts (0 on the bottom side), 364 nets.
